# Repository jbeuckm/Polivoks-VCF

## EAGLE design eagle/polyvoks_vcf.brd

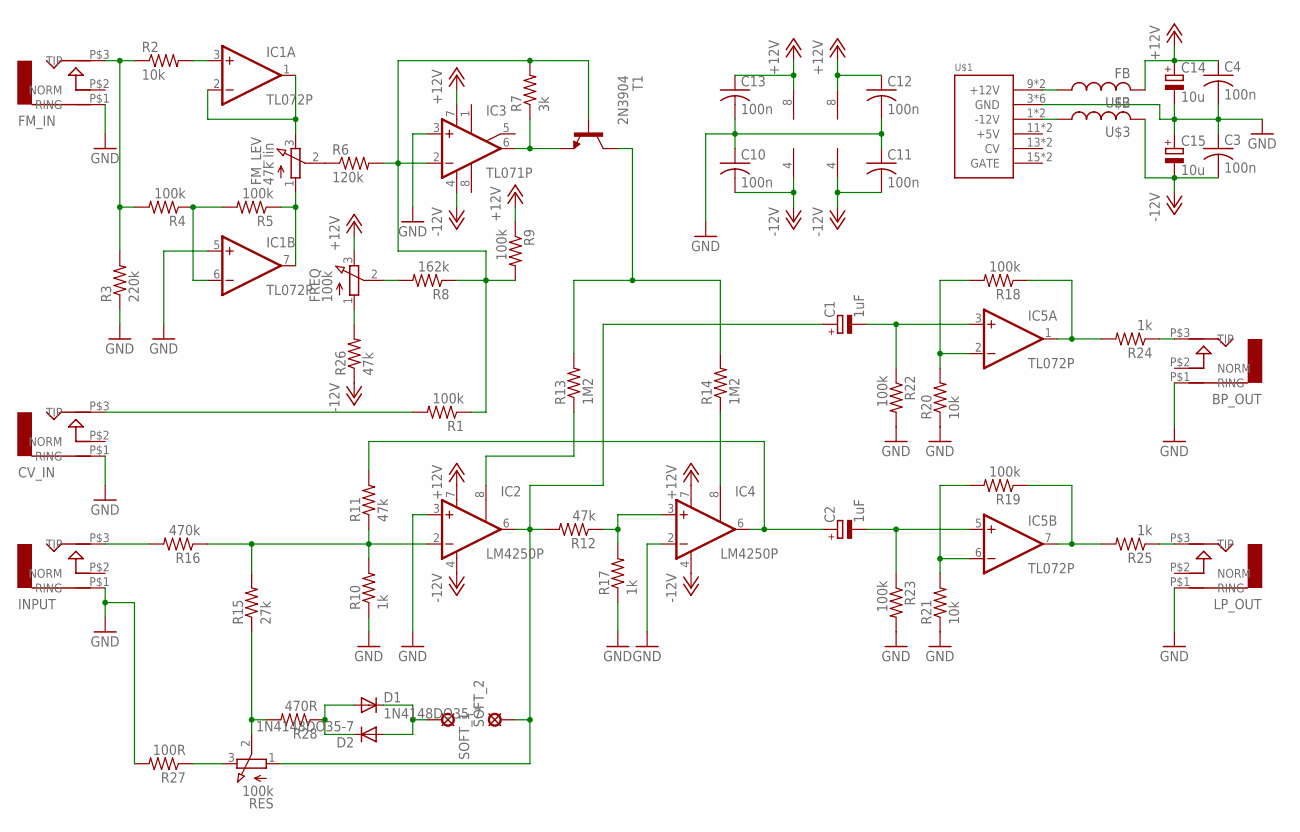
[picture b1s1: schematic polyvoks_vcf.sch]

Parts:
BP_OUT: AUDIO-JACK; ERTHENVAR-JACK-90DEG
C1, C2: 1uF; B45181C
C3, C4, C11, C12, C13: 100n; C050-024X044
C10: 100n; C075-032X103
C14, C15: 10u; B45181A
CV_IN: AUDIO-JACK; ERTHENVAR-JACK-90DEG
D1, D2: 1N4148DO35-7; DO35-7
FM_IN: AUDIO-JACK; ERTHENVAR-JACK-90DEG
FM_LEV: 47k lin; PTD901
FREQ: 100k; 3RP/1610N
IC1, IC5: TL072P; DIL08
IC2, IC4: LM4250P; DIL08
IC3: TL071P; DIL08
INPUT: AUDIO-JACK; ERTHENVAR-JACK-90DEG
LP_OUT: AUDIO-JACK; ERTHENVAR-JACK-90DEG
R1, R4, R5, R9, R18, R19, R22, R23: 100k; 0207/10
R2, R20, R21: 10k; 0207/10
R3: 220k; 0207/10
R6: 120k; 0207/10
R7: 3k; 0207/10
R8: 162k; 0207/10
R10, R17, R24, R25: 1k; 0207/10
R11, R12, R26: 47k; 0207/10
R13, R14: 1M2; 0207/10
R15: 27k; 0207/10
R16: 470k; 0207/10
R27: 100R; 0207/10
R28: 470R; 0207/10
RES: 100k; 3RP/1610N
SOFT_1, SOFT_2: LSP11
T1: 2N3904; TO92
U$1: POWER; POWER_16
U$2, U$3: FB

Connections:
+12V: C4.1, C12.1, C13.1, C14.+, FREQ.3 (E), IC1.8 (V+), IC2.7 (V+), IC3.7 (V+), IC4.7 (V+), IC5.8 (V+), R9.1, U$2.P$2 (2)
-12V: C3.2, C10.2, C11.2, C15.-, IC1.4 (V-), IC2.4 (V-), IC3.4 (V-), IC4.4 (V-), IC5.4 (V-), R26.1, U$3.P$2 (2)
unnamed: IC1.3 (+IN), R2.2
unnamed: FM_LEV.3 (E), IC1.1 (OUT), IC1.2 (-IN)
unnamed: FM_IN.P$3 (TIP), R2.1, R3.2, R4.2
unnamed: FREQ.2 (S), R8.2
unnamed: CV_IN.P$3 (TIP), R1.2
unnamed: FM_LEV.1 (A), IC1.7 (OUT), R5.1
unnamed: IC1.6 (-IN), R4.1, R5.2
unnamed: BP_OUT.P$3 (TIP), R24.1
unnamed: FM_LEV.2 (S), R6.1
unnamed: IC2.2 (-IN), R10.2, R11.1, R15.2, R16.1
unnamed: C2.+, IC4.6 (OUT), R11.2
unnamed: R15.1, R28.2, RES.2 (S)
unnamed: C1.+, IC2.6 (OUT), R12.2, RES.1 (A), SOFT_2.MP
unnamed: IC3.2 (-IN), R1.1, R6.2, R7.2, R8.1, R9.2, T1.2 (B)
unnamed: IC3.6 (OUT), R7.1, T1.3 (E)
unnamed: IC4.3 (+IN), R12.1, R17.2
unnamed: R13.2, R14.2, T1.1 (C)
unnamed: IC2.8 (ISET), R13.1
unnamed: IC4.8 (ISET), R14.1
unnamed: INPUT.P$3 (TIP), R16.2
unnamed: C1.-, IC5.3 (+IN), R22.1
unnamed: IC5.2 (-IN), R18.2, R20.2
unnamed: C2.-, IC5.5 (+IN), R23.1
unnamed: IC5.6 (-IN), R19.2, R21.2
unnamed: U$1.9 (+12V), U$1.10 (+12V), U$2.P$1 (1)
unnamed: U$1.1 (-12V), U$1.2 (-12V), U$3.P$1 (1)
unnamed: IC5.7 (OUT), R19.1, R25.2
unnamed: LP_OUT.P$3 (TIP), R25.1
unnamed: IC5.1 (OUT), R18.1, R24.2
unnamed: BP_OUT.P$1 (RING), C3.1, C4.2, C10.1, C11.1, C12.2, C13.2, C14.-, C15.+, CV_IN.P$1 (RING), FM_IN.P$1 (RING), IC1.5 (+IN), IC2.3 (+IN), IC3.3 (+IN), IC4.2 (-IN), INPUT.P$1 (RING), LP_OUT.P$1 (RING), R3.1, R10.1, R17.1, R20.1, R21.1, R22.2, R23.2, R27.2, U$1.3 (GND), U$1.4 (GND), U$1.5 (GND), U$1.6 (GND), U$1.7 (GND), U$1.8 (GND)
unnamed: R27.1, RES.3 (E)
unnamed: D1.A, D2.C, R28.1
unnamed: D1.C, D2.A, SOFT_1.MP
unnamed: FREQ.1 (A), R26.2

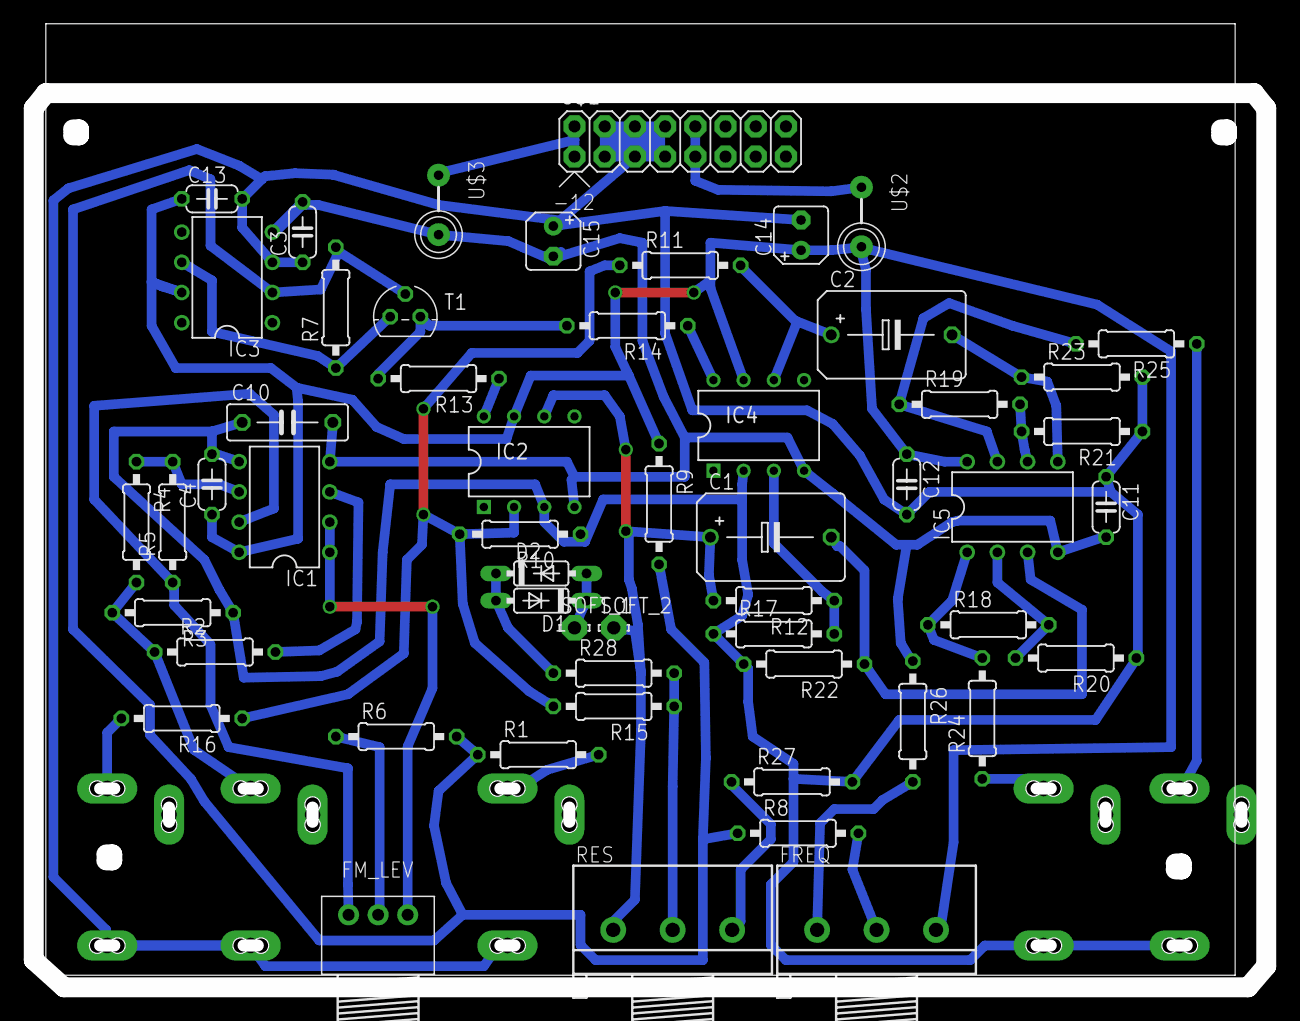
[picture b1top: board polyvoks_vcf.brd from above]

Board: 2 copper layers, 103.6 x 80.2 mm, 59 parts (0 on the bottom side), 36 nets.

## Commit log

2016-01-01 resonance corrected and minified
2016-01-05 panel
2016-01-26 schemo modded
2016-01-27 mods into layout
